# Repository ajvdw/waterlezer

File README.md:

# Waterlezer

### HomeAssistant
Waterlezer integrates your water meter seamlessly into Home Assistant. Plug and play, no coding necessary. It comes pre-installed with calibration firmware. After joining it to your WiFi it will, you can calibrate the device easily.
The WaterLezer is designed to work with any home automation system but the current integration is for HomeAssistant only.

### ESPHome
WaterLezer is powered by ESPHome. The code is opensource and can be found on my GitHub page for waterlezer. Here you can find a default yaml file as it is used for the precompiled firmware.

### How does it work
The waterlezer hardware is designed for detecting reflection from a metalic surface of a rotating wheel that is used for counting the number of liters of water flowing through the meter. It has an IR emitting LED and an IR sensitive phototransistor. It can output two digital signals to a microcontroller. Each signal can be set to a certain amount of reflection.  

### Installation
Push the sensor on the watermeter. Connect the waterlezer with the mcu. Connect the mcu to power (using a micro usb cable and phone charger).
Once powered-on it will behave like a wifi access point. Join the network with SSID Waterlezer. You will be forwarded to a webpage (http://192.168.4.1).
On this page you can configure your home wifi settings. If configured correctly it will join your home network automatically. 
Now you can connect the sensor to the mcu using the short cable and mount the sensor on top of the watermeter.

### Calibration
Open a tap and keep the water running when you are calibrating. 
On the PCB there are two potentiometers (blue boxes). Turn the left one all the way to the left and the right one all the way to the right.
Now slowly turn the left one to the right until the led starts flashing slowly on and off (no small flashes in between).
Next slowly turn the right one to the left until the led starts alternating between off-medium-on-medium-off etc.

The blue line in the graph below shows the reflection of the turning wheel of the meter. Calibration should result in the red line. 

The calibrated points are represented by an intersection between the vertical red lines and the blue curve (Horizontal lines through the yellow stars).

### Configuration
Now you can configure the watermeter in homeassistant. The ESPHome addon should be installed. 
I have included a sample yaml file (https://github.com/ajvdw/waterlezer/blob/main/esphome/waterlezer.yaml).
The easies way to start, is by adding a device (using the +). Don't copy the content of the yaml yet. Configure it by adding the name and wifi parameters of your home wifi. Select ESP8266 from the menu. A configuration yaml is generated. Edit the configuration to make sure that your device has a static IP address (https://esphome.io/components/wifi.html). Then create a binary file to upload to the waterlezer by selecting install and download the file.

The generated bin-file has to be uploaded the the waterlezer mcu manually by accessing the waterlezer-wifi and visit the 192.168.4.1 homepage. This page has an upload button to send the generated firmware to the device. If everything went well you can access the log of the device via homeassistant.
Finally you can modify the waterlezer.yaml and configuration.yaml with the yaml settings from the sample files. The current watermeter value can be entered using the utility_meter.calibration service under developer tools. The utility_meter integration takes care of retaining the values even when the waterlezer is rebooted or power cycled.

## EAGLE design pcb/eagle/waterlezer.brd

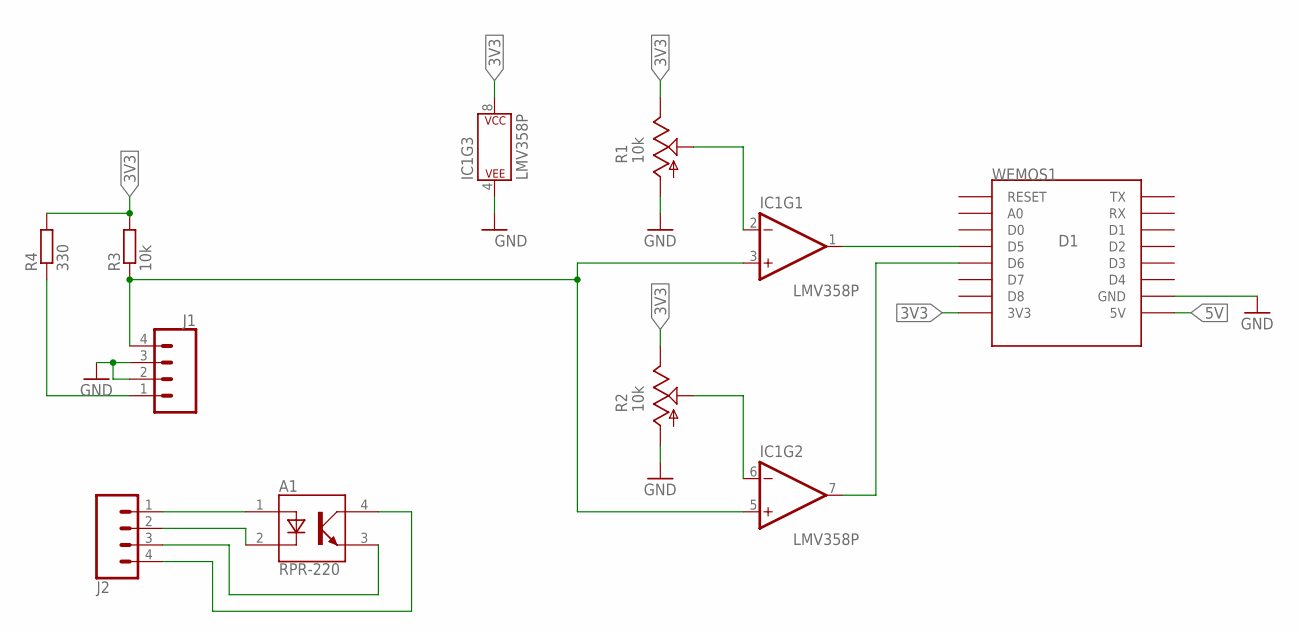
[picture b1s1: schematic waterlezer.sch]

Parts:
A1: RPR-220; PHODET_RPR-220
IC1: LMV358P; DIP08
J1, J2: CONN_04POLAR; MOLEX-1X4
R1, R2: 10k; S63P
R3: 10k; 0207/10
R4: 330; 0207/10
WEMOS1: D1; WEMOS-D1-MINI

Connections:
3V3: IC1.8 (P$V+), R1.E, R2.E, R3.2, R4.2, WEMOS1.3V3
5V: WEMOS1.5V
GND: IC1.4 (P$V-), J1.2, J1.3, R1.A, R2.A, WEMOS1.GND
unnamed: A1.4 (COLLECTOR), J2.4
unnamed: A1.2 (CATHODE), J2.2
unnamed: J1.1, R4.1
unnamed: A1.3 (EMITTER), J2.3
unnamed: A1.1 (ANODE), J2.1
unnamed: IC1.6 (-IN), R2.S
unnamed: IC1.2 (-IN), R1.S
unnamed: IC1.1 (OUT), WEMOS1.D5
unnamed: IC1.7 (OUT), WEMOS1.D6
unnamed: IC1.3 (+IN), IC1.5 (+IN), J1.4, R3.1

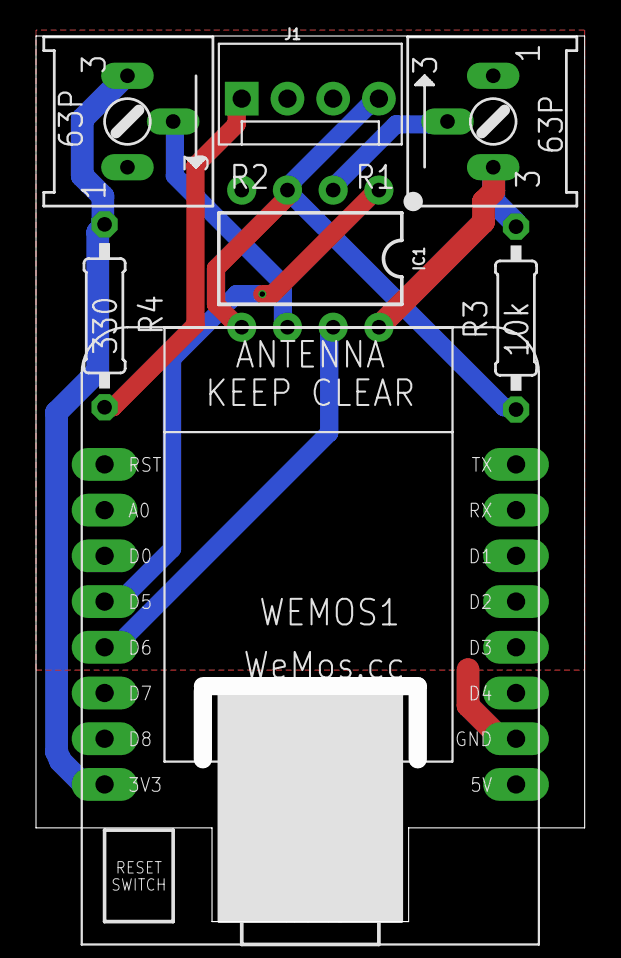
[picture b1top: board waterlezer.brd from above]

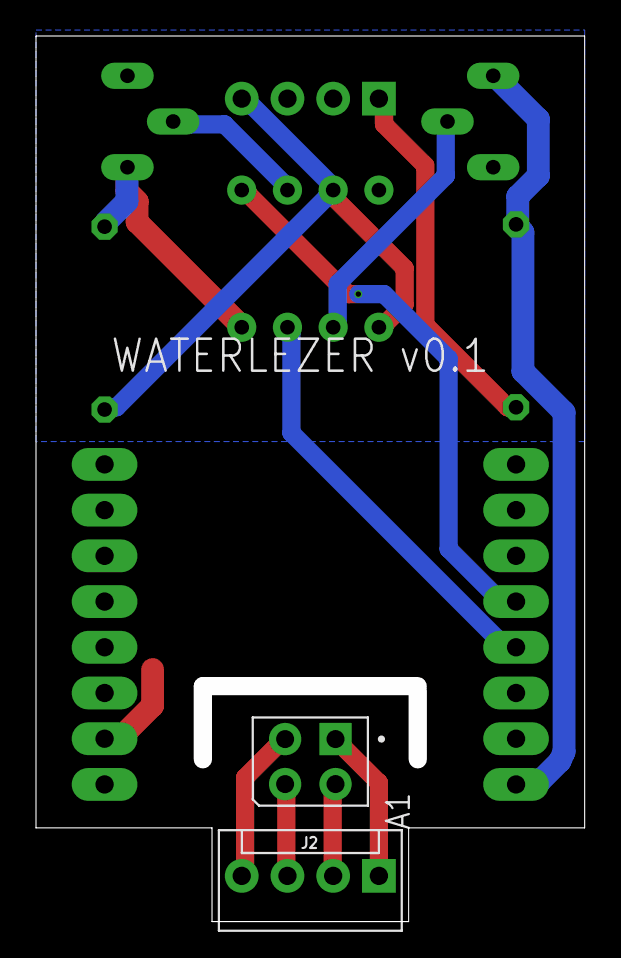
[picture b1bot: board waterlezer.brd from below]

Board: 2 copper layers, 29.5 x 48.2 mm, 9 parts (2 on the bottom side), 12 nets.

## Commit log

2021-10-21 Some config
2021-10-21 Cleaning up
2021-10-21 minor fixes
2021-10-21 simplyfied firmware
2021-10-21 full refresh
2021-10-21 moved custom component to its own repository
2021-10-22 minor changes
2021-10-22 cleanup
2021-10-23 added media
2021-10-23 reduced image size
2021-10-23 reduced material use
2021-10-26 Simplified
2021-10-26 improved yaml
2021-11-05 Removed reset of wifi settings
2021-11-10 Integrated with utility_meter to retain total values
2021-11-10 reduced size
2021-11-11 ESPHome Waterlezer firmware
2021-11-13 More space for rpr220
2022-11-10 Update waterlezer.yaml
    Added device class water for the energy dashboard in home assistant

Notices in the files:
parts and their libraries:
SparkFun-Connectors: Licensing: Creative Commons ShareAlike 4.0 International - https://creativecommons.org/licenses/by-sa/4.0
